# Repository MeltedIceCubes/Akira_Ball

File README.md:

# Current Target

- 2025/03/06
  - Lock down a basic functioning design.

# Ideas

- Sheet metal manufacturing?
- CNC Aluminum?

# PCB Parts

- [Voltage regulator](https://jlcpcb.com/partdetail/TexasInstruments-TPS73601DBVR/C59200)
-

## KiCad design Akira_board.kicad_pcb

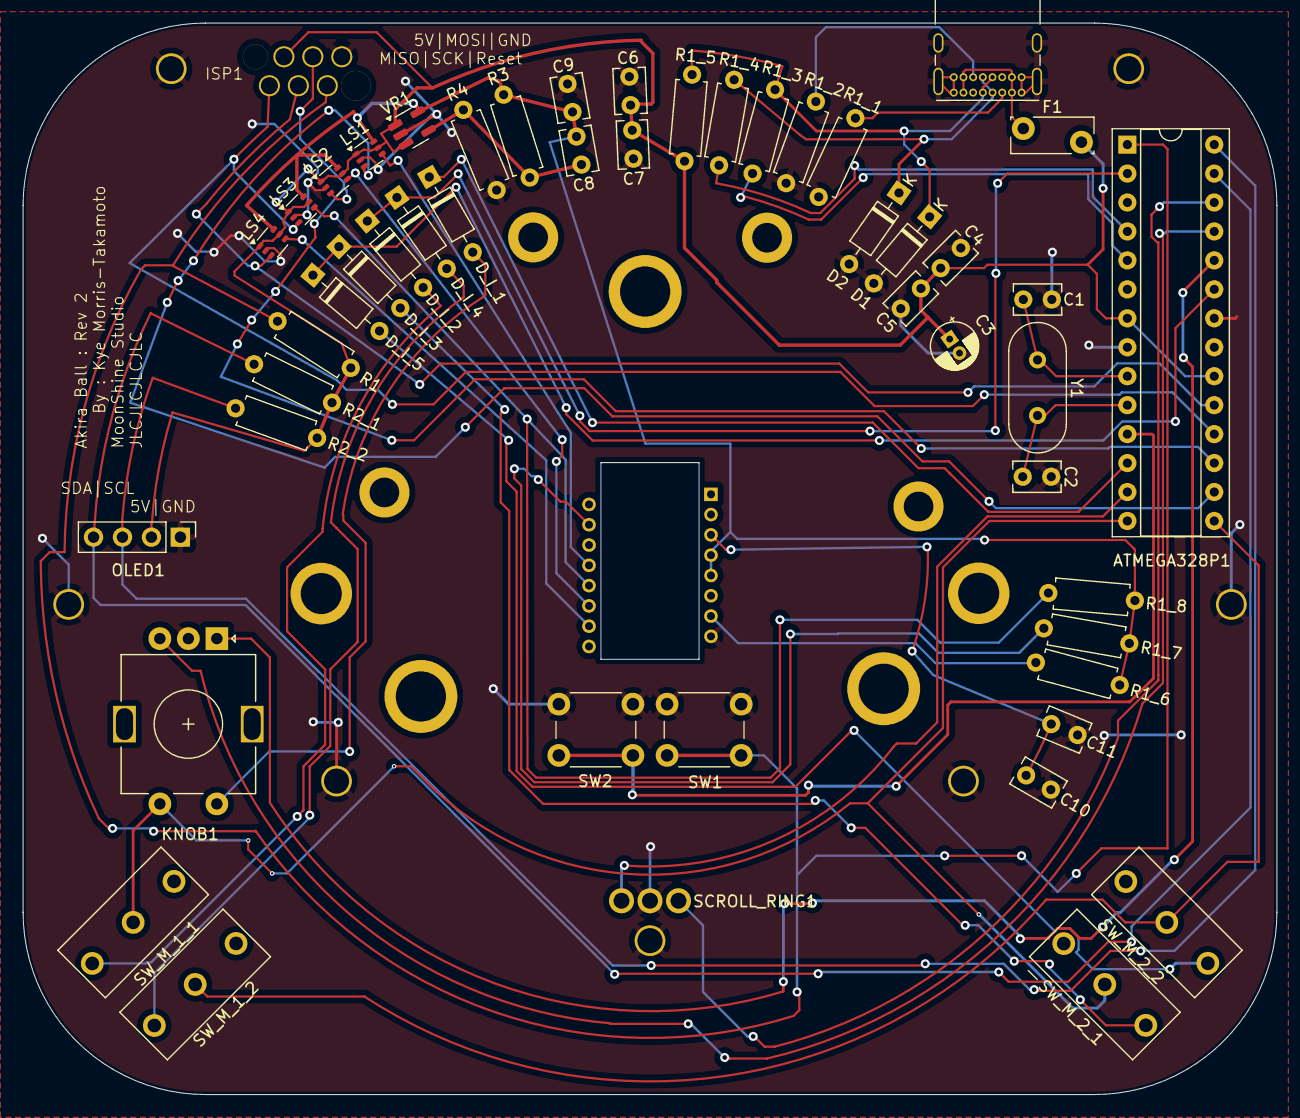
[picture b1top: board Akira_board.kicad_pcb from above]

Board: 2 copper layers, 110.0 x 94.0 mm, 58 parts (1 on the bottom side), 42 nets.

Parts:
ATMEGA328P1: ATMEGA328P-PU-ND; DIP-28_AtMega328PU
C1, C2: 22p; C_Rect_L4.0mm_W2.5mm_P2.50mm
C3: 4.7uF; CP_Radial_D4.0mm_P1.50mm
C4, C5, C6, C8, C9, C11: 100nF; C_Disc_D3.8mm_W2.6mm_P2.50mm
C7: 1uF; C_Rect_L4.0mm_W2.5mm_P2.50mm
C10: 4.7uF; C_Rect_L4.0mm_W2.5mm_P2.50mm
D1, D2: 3.6V; D_DO-35_SOD27_P7.62mm_Horizontal
D_I_1, D_I_2, D_I_3, D_I_4, D_I_5: D_Small; D_DO-35_SOD27_P7.62mm_Horizontal
F1: Polyfuse; Fuse_Bourns_MF-RG300
H1, H2, H3, H4, H5, H6, H7: MountingHole_Pad; M2 Mounting Hole
ISP1: AVR-ISP-6; SKEDD_6PinConnectingHole
KNOB1: Volume_Knob; RotaryEncoder_Alps_EC11E-Switch_Vertical_H20mm
LS1, LS2, LS3, LS4: SN74LVC1T45DCK; SOT-363_SC-70-6
OLED1: OLED_PinHeader_1x04_P2.54mm
PMW3360: PMW3360_2
R1: 10K; R_Axial_DIN0207_L6.3mm_D2.5mm_P7.62mm_Horizontal
R1_1, R1_2: 5.1k; R_Axial_DIN0207_L6.3mm_D2.5mm_P7.62mm_Horizontal
R1_3, R1_4: 75R; R_Axial_DIN0207_L6.3mm_D2.5mm_P7.62mm_Horizontal
R1_5: 1.5k; R_Axial_DIN0207_L6.3mm_D2.5mm_P7.62mm_Horizontal
R1_6, R1_8: 10k; R_Axial_DIN0207_L6.3mm_D2.5mm_P7.62mm_Horizontal
R1_7: 39R; R_Axial_DIN0207_L6.3mm_D2.5mm_P7.62mm_Horizontal
R2_1, R2_2: 4.7K; R_Axial_DIN0207_L6.3mm_D2.5mm_P7.62mm_Horizontal
R3: 37.4K; R_Axial_DIN0207_L6.3mm_D2.5mm_P7.62mm_Horizontal
R4: 63.4K; R_Axial_DIN0207_L6.3mm_D2.5mm_P7.62mm_Horizontal
SCROLL_RING1: Rotary_Encoder; Encoder_Ring
SW1: Reset SW; SW_PUSH_6mm
SW2: Boot SW; SW_PUSH_6mm
SW_M_1_1, SW_M_1_2, SW_M_2_1, SW_M_2_2: Kailh_MicroSwitch; GM8.0
USB1: USB_C_Receptacle_USB2.0; USB_C_Receptacle_GCT_USB4085
VR1: TPS73601DBV; SOT-23-5
Y1: 16MHz; Crystal_HC49-4H_Vertical

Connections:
+5V: ATMEGA328P1.7 (VCC), ATMEGA328P1.20 (AVCC), C3.1, C4.1, C5.1, C6.1, C7.1, F1.2, ISP1.2 (VCC), LS1.1 (VCCA), LS1.5 (DIR), LS2.1 (VCCA), LS2.5 (DIR), LS3.1 (VCCA), LS3.5 (DIR), LS4.1 (VCCA), LS4.5 (DIR), OLED1.2 (VCC), R1.2, R1_5.2, R2_1.1, R2_2.2, VR1.1 (IN), VR1.3 (EN)
BOOT: ATMEGA328P1.11 (PD5), SW2.1
COL0: ATMEGA328P1.14 (PB0), KNOB1.S1, SW_M_1_1.NO, SW_M_2_1.NO
COL1: ATMEGA328P1.15 (PB1), SW_M_1_2.NO, SW_M_2_2.NO
CRYSTAL+: ATMEGA328P1.10 (PB7), C2.2, Y1.2
CRYSTAL-: ATMEGA328P1.9 (PB6), C1.2, Y1.1
D+: ATMEGA328P1.4 (PD2), R1_4.2
D-: ATMEGA328P1.5 (PD3), R1_3.1
GND: ATMEGA328P1.8 (GND), ATMEGA328P1.22 (GND), C1.1, C2.1, C3.2, C4.2, C5.2, C6.2, C7.2, C9.2, C10.2, C11.2, D1.2 (A), D2.2 (A), H1.1, H2.1, H3.1, H4.1, H5.1, H6.1, H7.1, ISP1.6 (GND), KNOB1.C, LS1.2 (GND), LS2.2 (GND), LS3.2 (GND), LS4.2 (GND), OLED1.1 (GND), PMW3360.8 (GND), R1_1.1, R1_2.2, R4.2, SCROLL_RING1.C, SW1.2, SW2.2, USB1.A1 (GND), USB1.A12 (GND), USB1.B1 (GND), USB1.B12 (GND), USB1.S1 (SHIELD), VR1.2 (GND)
I2C_SCL: ATMEGA328P1.28 (PC5), OLED1.3 (SCL), R2_2.1
I2C_SDA: ATMEGA328P1.27 (PC4), OLED1.4 (SDA), R2_1.2
MISO: ATMEGA328P1.18 (PB4), ISP1.1 (MISO), LS3.3 (A)
MOSI: ATMEGA328P1.17 (PB3), ISP1.4 (MOSI), LS2.3 (A)
NCS: ATMEGA328P1.16 (PB2), LS1.3 (A)
unnamed: D1.1 (K), R1_3.2, R1_5.1, USB1.A7 (D-), USB1.B7 (D-)
unnamed: D2.1 (K), R1_4.1, USB1.A6 (D+), USB1.B6 (D+)
unnamed: D_I_1.2 (A), KNOB1.S2
unnamed: D_I_2.2 (A), SW_M_1_1.COM
unnamed: D_I_3.2 (A), SW_M_2_1.COM
unnamed: D_I_4.2 (A), SW_M_1_2.COM
unnamed: D_I_5.2 (A), SW_M_2_2.COM
unnamed: F1.1, USB1.A4 (VBUS), USB1.A9 (VBUS), USB1.B4 (VBUS), USB1.B9 (VBUS)
unnamed: PMW3360.15 (LED_P), R1_7.2
unnamed: PMW3360.7 (NRESET), R1_6.2
unnamed: C10.1, C11.1, PMW3360.3 (VDDPIX)
unnamed: R1_1.2, USB1.A5 (CC1)
unnamed: R1_2.1, USB1.B5 (CC2)
unnamed: C8.2, R3.2, R4.1, VR1.4 (FB)
PMW.MISO: LS3.4 (B), PMW3360.12 (MISO), R1_8.2
PMW.MOSI: LS2.4 (B), PMW3360.11 (MOSI)
PMW.NCS: LS1.4 (B), PMW3360.13 (NCS)
PMW.SCK: LS4.4 (B), PMW3360.10 (SCLK)
RESET: ATMEGA328P1.1 (PC6), ISP1.5 (~RST), R1.1, SW1.1
RING_A: ATMEGA328P1.13 (PD7), SCROLL_RING1.A
RING_B: ATMEGA328P1.26 (PC3), SCROLL_RING1.B
ROW0: ATMEGA328P1.12 (PD6), D_I_1.1 (K)
ROW1: ATMEGA328P1.2 (PD0), D_I_2.1 (K), D_I_4.1 (K)
ROW2: ATMEGA328P1.23 (PC0), D_I_3.1 (K), D_I_5.1 (K)
SCK: ATMEGA328P1.19 (PB5), ISP1.3 (SCK), LS4.3 (A)
VDD: C8.1, C9.1, LS1.6 (VCCB), LS2.6 (VCCB), LS3.6 (VCCB), LS4.6 (VCCB), PMW3360.4 (VDD), PMW3360.5 (VDDIO), R1_6.1, R1_7.1, R1_8.1, R3.1, VR1.5 (OUT)
VK_A: ATMEGA328P1.24 (PC1), KNOB1.A
VK_B: ATMEGA328P1.25 (PC2), KNOB1.B

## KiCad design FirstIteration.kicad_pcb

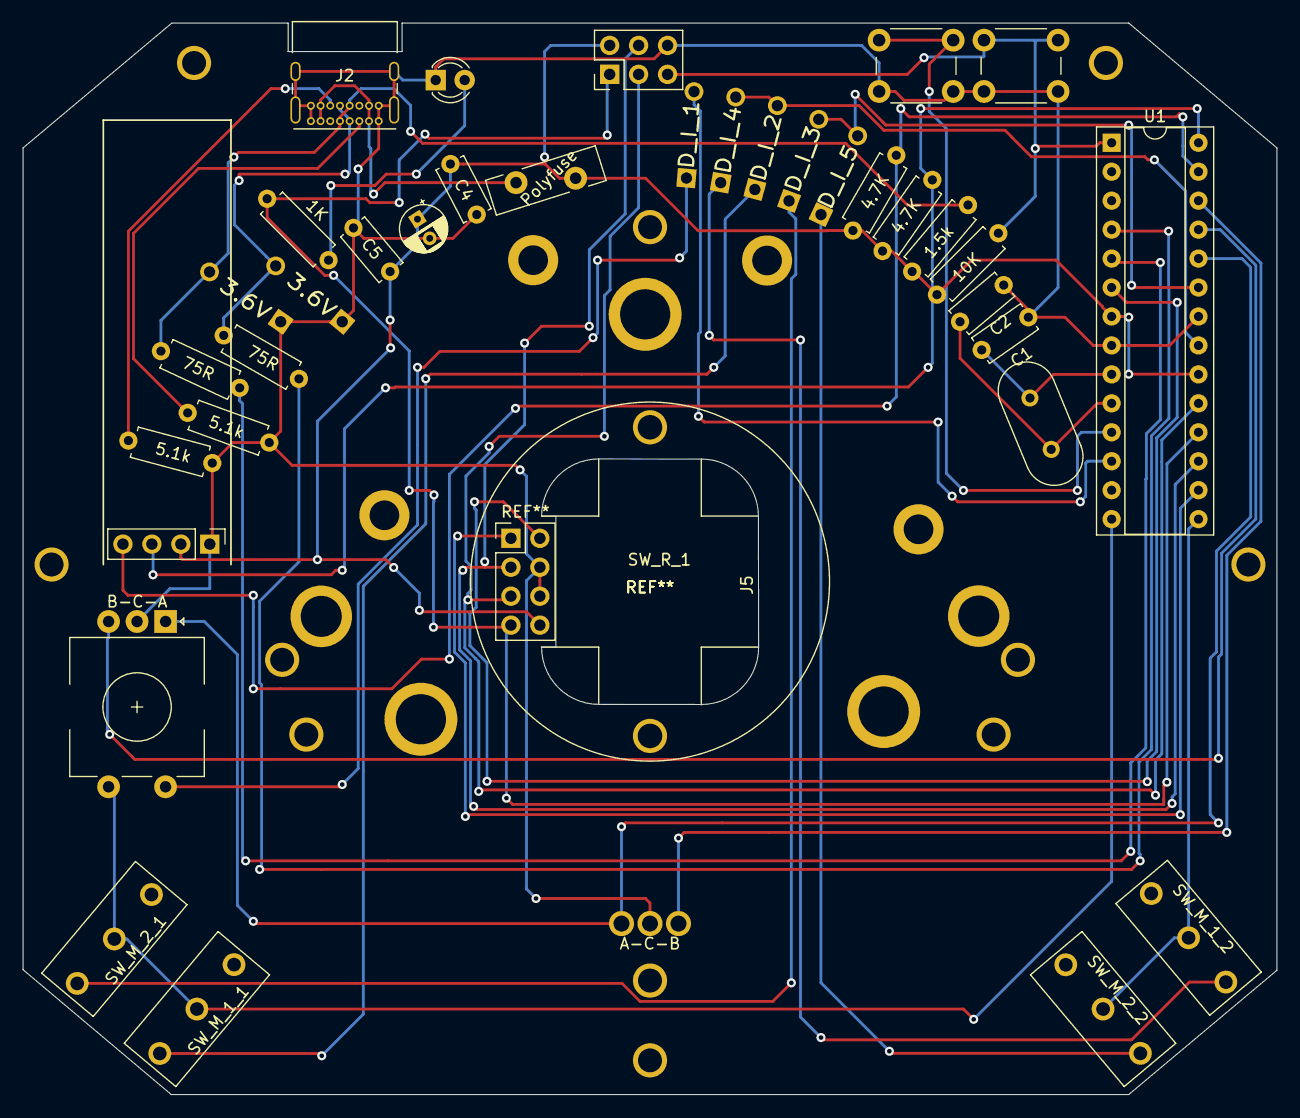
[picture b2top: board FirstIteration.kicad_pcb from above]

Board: 2 copper layers, 110.0 x 94.0 mm, 37 parts (0 on the bottom side), 34 nets.

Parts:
C1, C2: 20p; C_Disc_D5.0mm_W2.5mm_P5.00mm
C3: 4.7u; CP_Radial_D4.0mm_P2.00mm
C4, C5: 100n; C_Disc_D5.0mm_W2.5mm_P5.00mm
D1, D2: 3.6V; Diode
D4: LED; LED_D3.0mm_Clear
D_I_1, D_I_2, D_I_3, D_I_4, D_I_5: D_Small; Diode
F1: Polyfuse; Fuse_Bourns_MF-RG400
J1: AVR-ISP-6; PinHeader_2x03_P2.54mm_Vertical
J2: USB_C_Receptacle_USB2.0; USB_C_Receptacle_GCT_USB4085
J3: Conn_01x04; PinHeader_1x04_P2.54mm_Vertical
J5: Conn_02x04_Odd_Even; ADNS-9800
R1: 10K; R_Axial_DIN0207_L6.3mm_D2.5mm_P7.62mm_Horizontal
R1_1, R1_2: 5.1k; R_Axial_DIN0207_L6.3mm_D2.5mm_P7.62mm_Horizontal
R1_3, R1_4: 75R; R_Axial_DIN0207_L6.3mm_D2.5mm_P7.62mm_Horizontal
R1_5: 1.5k; R_Axial_DIN0207_L6.3mm_D2.5mm_P7.62mm_Horizontal
R2: 1K; R_Axial_DIN0207_L6.3mm_D2.5mm_P7.62mm_Horizontal
R2_1, R2_2: 4.7K; R_Axial_DIN0207_L6.3mm_D2.5mm_P7.62mm_Horizontal
SW1: Reset SW; SW_PUSH_6mm
SW2: Boot SW; SW_PUSH_6mm
SW_M_1_1, SW_M_1_2, SW_M_2_1, SW_M_2_2: Kailh_MicroSwitch; GM8.0
SW_R_1: Rotary_Encoder; Encoder_Ring
SW_V_1: Volume_Knob; RotaryEncoder_EC11
U1: ATMEGA328P-PU-ND; DIP-28_W7.62mm_Socket
Y1: 16MHz; Crystal_HC49-U_Vertical

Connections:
+5V: C3.1, C4.1, C5.1, F1.2, J1.2, J3.2, J5.8, R1.2, R1_5.2, R2_1.1, R2_2.2, U1.7, U1.20
BOOT: SW2.1, U1.11
COL0: SW_M_1_1.NO, SW_M_2_1.NO, SW_V_1.S1, U1.14
COL1: SW_M_1_2.NO, SW_M_2_2.NO, U1.15
D+: R1_4.2, U1.4
D-: R1_3.1, U1.5
GND: C1.1, C2.1, C3.2, C4.2, C5.2, D1.2, D2.2, D4.1, J1.6, J2.A1, J2.A12, J2.B1, J2.B12, J2.S1, J3.1, J5.4, J5.6, R1_1.1, R1_2.2, SW1.2, SW2.2, SW_R_1.C, SW_V_1.C, U1.8, U1.22
I2C_SCL: J3.3, R2_2.1, U1.28
I2C_SDA: J3.4, R2_1.2, U1.27
MI: J1.1, J5.7, R2.2, U1.18
MO: J1.4, J5.3, U1.17
MOT: J5.2, U1.6
unnamed: C1.2, U1.9, Y1.1
unnamed: C2.2, U1.10, Y1.2
unnamed: D1.1, J2.A7, J2.B7, R1_3.2, R1_5.1
unnamed: D2.1, J2.A6, J2.B6, R1_4.1
unnamed: D4.2, R2.1
unnamed: D_I_1.2, SW_V_1.S2
unnamed: D_I_2.2, SW_M_1_1.COM
unnamed: D_I_3.2, SW_M_2_1.COM
unnamed: D_I_4.2, SW_M_1_2.COM
unnamed: D_I_5.2, SW_M_2_2.COM
unnamed: F1.1, J2.A4, J2.A9, J2.B4, J2.B9
unnamed: J2.A5, R1_1.2
unnamed: J2.B5, R1_2.1
RESET: J1.5, R1.1, SW1.1, U1.1
RING_A: SW_R_1.A, SW_V_1.A, U1.24
RING_B: SW_R_1.B, U1.26
ROW0: D_I_1.1, U1.12
ROW1: D_I_2.1, D_I_4.1, U1.21
ROW2: D_I_3.1, D_I_5.1, U1.23
SC: J1.3, J5.5, U1.19
SS: J5.1, U1.16
VK_B: SW_V_1.B, U1.25

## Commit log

2023-09-21 First commit. Just file dumping
2023-10-26 Poster Stuff
2025-03-08 adding sensor directly
2025-03-28 Before PCB layout
2025-03-28 reduced files
2025-04-02 nice corners designed
2025-04-08 Before routing PCB
2025-04-08 Done board setup
2025-09-26 Dump
2026-01-31 Save
2026-05-31 Before PCB Fix
2026-06-05 Save for now
2026-06-10 SMT (done hopefully)
2026-06-10 fixed switch locations
